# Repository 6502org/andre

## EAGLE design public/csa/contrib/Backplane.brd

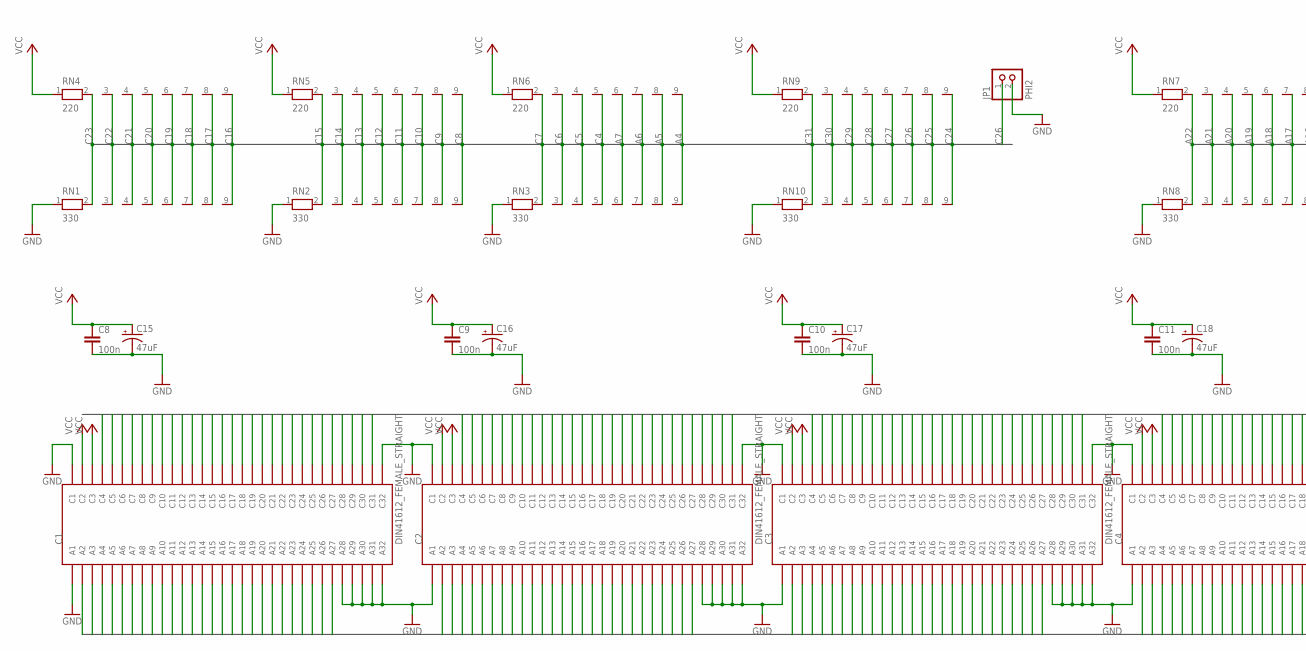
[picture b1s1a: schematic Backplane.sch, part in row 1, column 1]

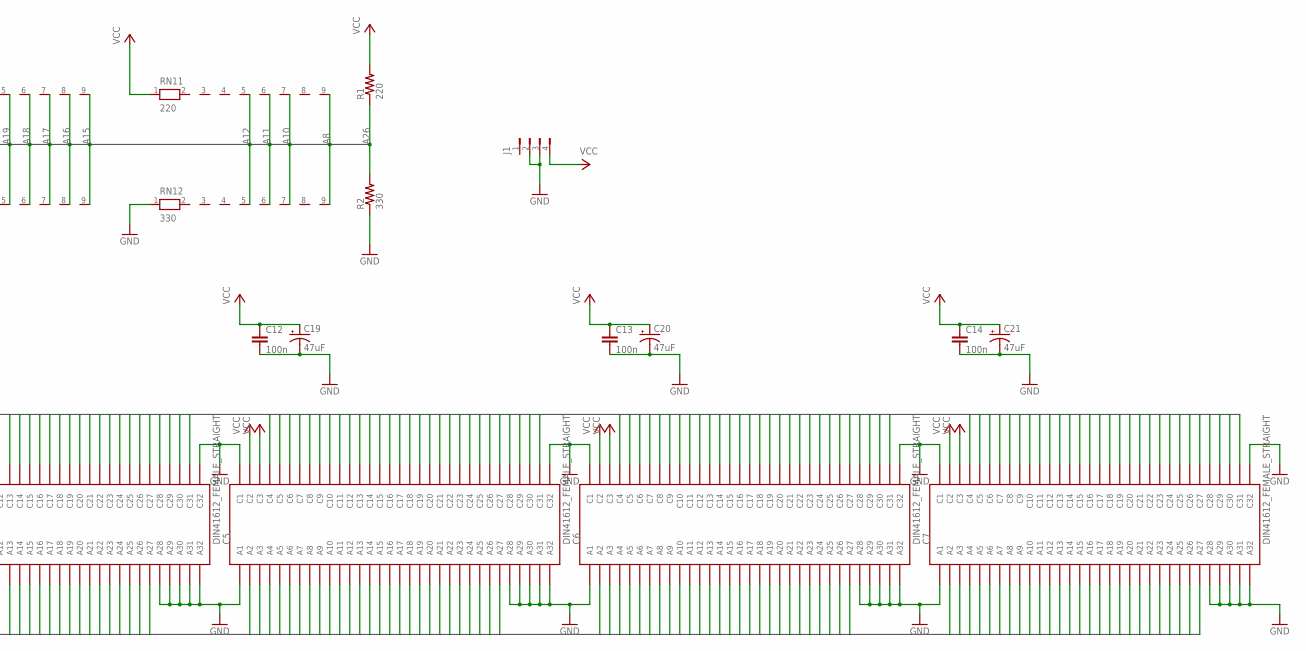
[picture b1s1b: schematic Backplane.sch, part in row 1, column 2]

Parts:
C1, C2, C3, C4, C5, C6, C7: DIN41612_FEMALE_STRAIGHT
C8, C9, C10, C11, C12, C13, C14: 100n; C025-025X050
C15, C16, C17, C18, C19, C20, C21: 47uF; E2,5-7
J1: FLOPPY-4350211; 350211
JP1: PHI2; 1X02
R1: 220; 0204/5
R2: 330; 0204/5
RN1, RN2, RN3, RN8, RN10, RN12: 330; RN-9
RN4, RN5, RN6, RN7, RN9, RN11: 220; RN-9

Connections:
A2: C1.A2, C2.A2, C3.A2, C4.A2, C5.A2, C6.A2, C7.A2
A3: C1.A3, C2.A3, C3.A3, C4.A3, C5.A3, C6.A3, C7.A3
A4: C1.A4, C2.A4, C3.A4, C4.A4, C5.A4, C6.A4, C7.A4, RN3.9, RN6.9
A5: C1.A5, C2.A5, C3.A5, C4.A5, C5.A5, C6.A5, C7.A5, RN3.8, RN6.8
A6: C1.A6, C2.A6, C3.A6, C4.A6, C5.A6, C6.A6, C7.A6, RN3.7, RN6.7
A7: C1.A7, C2.A7, C3.A7, C4.A7, C5.A7, C6.A7, C7.A7, RN3.6, RN6.6
A8: C1.A8, C2.A8, C3.A8, C4.A8, C5.A8, C6.A8, C7.A8, RN11.9, RN12.9
A9: C1.A9, C2.A9, C3.A9, C4.A9, C5.A9, C6.A9, C7.A9
A10: C1.A10, C2.A10, C3.A10, C4.A10, C5.A10, C6.A10, C7.A10, RN11.7, RN12.7
A11: C1.A11, C2.A11, C3.A11, C4.A11, C5.A11, C6.A11, C7.A11, RN11.6, RN12.6
A12: C1.A12, C2.A12, C3.A12, C4.A12, C5.A12, C6.A12, C7.A12, RN11.5, RN12.5
A13: C1.A13, C2.A13, C3.A13, C4.A13, C5.A13, C6.A13, C7.A13
A14: C1.A14, C2.A14, C3.A14, C4.A14, C5.A14, C6.A14, C7.A14
A15: C1.A15, C2.A15, C3.A15, C4.A15, C5.A15, C6.A15, C7.A15, RN7.9, RN8.9
A16: C1.A16, C2.A16, C3.A16, C4.A16, C5.A16, C6.A16, C7.A16, RN7.8, RN8.8
A17: C1.A17, C2.A17, C3.A17, C4.A17, C5.A17, C6.A17, C7.A17, RN7.7, RN8.7
A18: C1.A18, C2.A18, C3.A18, C4.A18, C5.A18, C6.A18, C7.A18, RN7.6, RN8.6
A19: C1.A19, C2.A19, C3.A19, C4.A19, C5.A19, C6.A19, C7.A19, RN7.5, RN8.5
A20: C1.A20, C2.A20, C3.A20, C4.A20, C5.A20, C6.A20, C7.A20, RN7.4, RN8.4
A21: C1.A21, C2.A21, C3.A21, C4.A21, C5.A21, C6.A21, C7.A21, RN7.3, RN8.3
A22: C1.A22, C2.A22, C3.A22, C4.A22, C5.A22, C6.A22, C7.A22, RN7.2, RN8.2
A23: C1.A23, C2.A23, C3.A23, C4.A23, C5.A23, C6.A23, C7.A23
A24: C1.A24, C2.A24, C3.A24, C4.A24, C5.A24, C6.A24, C7.A24
A25: C1.A25, C2.A25, C3.A25, C4.A25, C5.A25, C6.A25, C7.A25
A26: C1.A26, C2.A26, C3.A26, C4.A26, C5.A26, C6.A26, C7.A26, R1.1, R2.2
A27: C1.A27, C2.A27, C3.A27, C4.A27, C5.A27, C6.A27, C7.A27
C4: C1.C4, C2.C4, C3.C4, C4.C4, C5.C4, C6.C4, C7.C4, RN3.5, RN6.5
C5: C1.C5, C2.C5, C3.C5, C4.C5, C5.C5, C6.C5, C7.C5, RN3.4, RN6.4
C6: C1.C6, C2.C6, C3.C6, C4.C6, C5.C6, C6.C6, C7.C6, RN3.3, RN6.3
C7: C1.C7, C2.C7, C3.C7, C4.C7, C5.C7, C6.C7, C7.C7, RN3.2, RN6.2
C8: C1.C8, C2.C8, C3.C8, C4.C8, C5.C8, C6.C8, C7.C8, RN2.9, RN5.9
C9: C1.C9, C2.C9, C3.C9, C4.C9, C5.C9, C6.C9, C7.C9, RN2.8, RN5.8
C10: C1.C10, C2.C10, C3.C10, C4.C10, C5.C10, C6.C10, C7.C10, RN2.7, RN5.7
C11: C1.C11, C2.C11, C3.C11, C4.C11, C5.C11, C6.C11, C7.C11, RN2.6, RN5.6
C12: C1.C12, C2.C12, C3.C12, C4.C12, C5.C12, C6.C12, C7.C12, RN2.5, RN5.5
C13: C1.C13, C2.C13, C3.C13, C4.C13, C5.C13, C6.C13, C7.C13, RN2.4, RN5.4
C14: C1.C14, C2.C14, C3.C14, C4.C14, C5.C14, C6.C14, C7.C14, RN2.3, RN5.3
C15: C1.C15, C2.C15, C3.C15, C4.C15, C5.C15, C6.C15, C7.C15, RN2.2, RN5.2
C16: C1.C16, C2.C16, C3.C16, C4.C16, C5.C16, C6.C16, C7.C16, RN1.9, RN4.9
C17: C1.C17, C2.C17, C3.C17, C4.C17, C5.C17, C6.C17, C7.C17, RN1.8, RN4.8
C18: C1.C18, C2.C18, C3.C18, C4.C18, C5.C18, C6.C18, C7.C18, RN1.7, RN4.7
C19: C1.C19, C2.C19, C3.C19, C4.C19, C5.C19, C6.C19, C7.C19, RN1.6, RN4.6
C20: C1.C20, C2.C20, C3.C20, C4.C20, C5.C20, C6.C20, C7.C20, RN1.5, RN4.5
C21: C1.C21, C2.C21, C3.C21, C4.C21, C5.C21, C6.C21, C7.C21, RN1.4, RN4.4
C22: C1.C22, C2.C22, C3.C22, C4.C22, C5.C22, C6.C22, C7.C22, RN1.3, RN4.3
C23: C1.C23, C2.C23, C3.C23, C4.C23, C5.C23, C6.C23, C7.C23, RN1.2, RN4.2
C24: C1.C24, C2.C24, C3.C24, C4.C24, C5.C24, C6.C24, C7.C24, RN9.9, RN10.9
C25: C1.C25, C2.C25, C3.C25, C4.C25, C5.C25, C6.C25, C7.C25, RN9.8, RN10.8
C26: C1.C26, C2.C26, C3.C26, C4.C26, C5.C26, C6.C26, C7.C26, JP1.1, RN9.7, RN10.7
C27: C1.C27, C2.C27, C3.C27, C4.C27, C5.C27, C6.C27, C7.C27, RN9.6, RN10.6
C28: C1.C28, C2.C28, C3.C28, C4.C28, C5.C28, C6.C28, C7.C28, RN9.5, RN10.5
C29: C1.C29, C2.C29, C3.C29, C4.C29, C5.C29, C6.C29, C7.C29, RN9.4, RN10.4
C30: C1.C30, C2.C30, C3.C30, C4.C30, C5.C30, C6.C30, C7.C30, RN9.3, RN10.3
C31: C1.C31, C2.C31, C3.C31, C4.C31, C5.C31, C6.C31, C7.C31, RN9.2, RN10.2
GND: C1.A1, C1.A28, C1.A29, C1.A30, C1.A31, C1.A32, C1.C1, C1.C32, C2.A1, C2.A28, C2.A29, C2.A30, C2.A31, C2.A32, C2.C1, C2.C32, C3.A1, C3.A28, C3.A29, C3.A30, C3.A31, C3.A32, C3.C1, C3.C32, C4.A1, C4.A28, C4.A29, C4.A30, C4.A31, C4.A32, C4.C1, C4.C32, C5.A1, C5.A28, C5.A29, C5.A30, C5.A31, C5.A32, C5.C1, C5.C32, C6.A1, C6.A28, C6.A29, C6.A30, C6.A31, C6.A32, C6.C1, C6.C32, C7.A1, C7.A28, C7.A29, C7.A30, C7.A31, C7.A32, C7.C1, C7.C32, C8.2, C9.2, C10.2, C11.2, C12.2, C13.2, C14.2, C15.-, C16.-, C17.-, C18.-, C19.-, C20.-, C21.-, J1.2, J1.3, JP1.2, R2.1, RN1.1, RN2.1, RN3.1, RN8.1, RN10.1, RN12.1
VCC: C1.C2, C1.C3, C2.C2, C2.C3, C3.C2, C3.C3, C4.C2, C4.C3, C5.C2, C5.C3, C6.C2, C6.C3, C7.C2, C7.C3, C8.1, C9.1, C10.1, C11.1, C12.1, C13.1, C14.1, C15.+, C16.+, C17.+, C18.+, C19.+, C20.+, C21.+, J1.4, R1.2, RN4.1, RN5.1, RN6.1, RN7.1, RN9.1, RN11.1

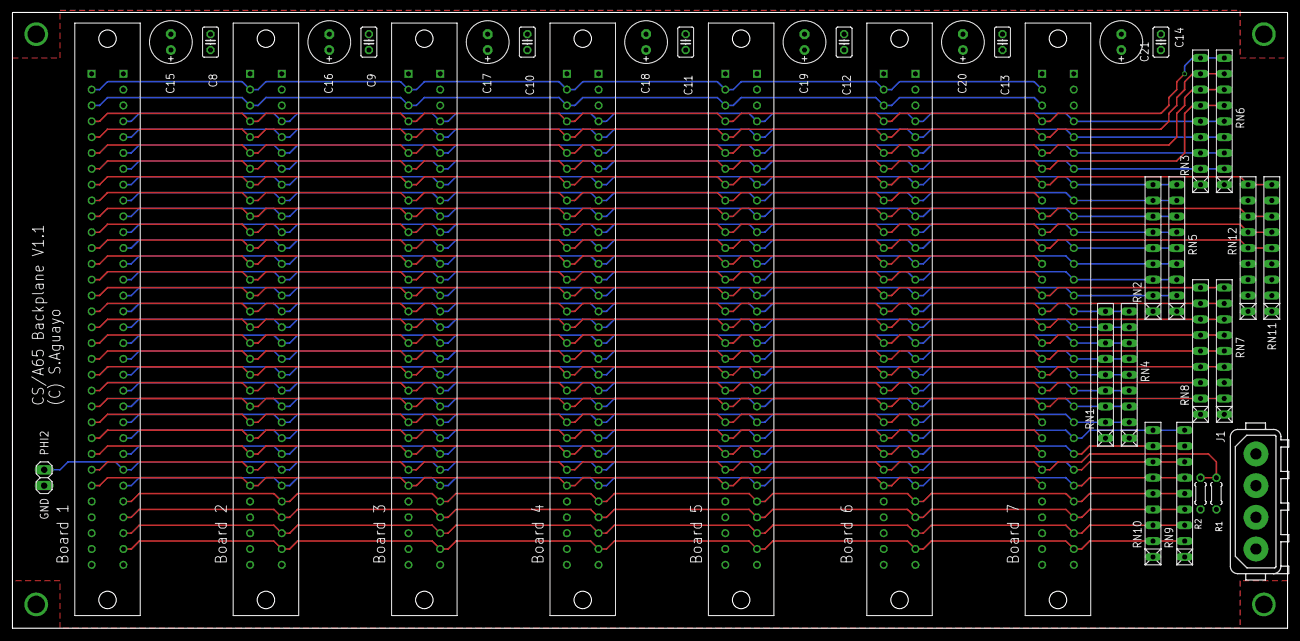
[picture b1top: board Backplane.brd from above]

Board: 2 copper layers, 204.4 x 98.7 mm, 37 parts (0 on the bottom side), 56 nets.
